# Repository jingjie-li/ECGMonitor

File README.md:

# Overview
This is a ECG/SPO2 Monitor Project. We mainly used TI's (Texas Instrument) [ADS1293](http://www.ti.com/product/ads1293)/[AFE4400](http://www.ti.com/product/AFE4400/description) analog front-end IC to acquire physiology data form human body, and used TI's [MSP430F149 MCU](http://www.ti.com/product/MSP430F149/description) to control these Chips, and send the data to our Android Smartphone App via TI's Bluetooth IC [CC2540](http://www.ti.com/product/CC2540/description). In our smartphone App, we can display ECG/PPG wavefore, compute & display SPO2,Heart Rate, and Heart Rate Variability(HRV), and control the hardware to running on different acquision mode (such as 3-Leads or 5-Leads mode).

To do so, we disigned and made a custome PCB using Autodesk EAGLE, did embedded system programing for MSP430 using IAR IDE, and some stuff about smartphone APP. We also had a 3D printed case for our circuit.

The major advantages of our system, is our outstanding power consumption performance. Our hardware only took about 300mW Power for Li-ion battery (about ~180mW for bluetooth). Also, our PCB is super portable, size less than 10-by-10cm.

We Shared the majority of our code and design files. Including MSP430 program, PCB layout, 3D printing models, and some APP code.

We do these stuff is for a [National BME(Biomedical Engineering) Competition for College Students](http://bmedesign.medmeeting.org/cn) in ShenZhen, China.

__On Aug 28, 2018: We just won the FIRST PRIZE in [National BME(Biomedical Engineering) Competition for College Students](http://bmedesign.medmeeting.org/cn) in ShenZhen, China. Which is the HIGHEST AWARD.__

__Fig 1 Our First Prize Trophy and Certification__

# Quick access of our sub-modules
+ [Main MCU Controling Code](https://github.com/celelion/ECGMonitor/blob/master/MSP430/AFE%26ADS_inter/main.c)
+ [PCB Layout](https://github.com/celelion/ECGMonitor/tree/master/PCB)
+ [APP](https://github.com/celelion/ECGMonitor/tree/master/APP_Design)
+ [3D Printed PCB Case](https://github.com/celelion/ECGMonitor/tree/master/Case)
+ [Processing Tools for Computer Debugging](https://github.com/celelion/ECGMonitor/tree/master/Analog_Front/EEGPPGdataRecTest)
+ [Arduino DUE based IC chip(ADS1293/AFE4400) SPI interface verification code](https://github.com/celelion/ECGMonitor/tree/master/Analog_Front/Arduino-TestFirmware)

# Features
## Characteristics and Technical Indexes
### ECG

+ Differential Input Voltage Range: -400 mV ~ +400 mV
+ Common-Mode Rejection Ratio(CMRR): >100 dB
+ Differential Input Resistance: 500 MΩ
+ Sampling Rate: 150 Hz

### Oximeter
+ Sampling Rate: 50 Hz

### Power Consumption
| Overall Power | Bluetooth | ADS-ECG Module | AFE-Oximeter Module | MSP430-MCU Module |
| ------ | ------ | ------ | ------ | ------ |
| 291.1103 mW | 177.7327 mW | 3.1984 mW | 93.0931 mW | 17.0861 mW |

# Development Team
+ Jingjie Li (jingjie.li.21@ucl.ac.uk) - Hardware, PCB Layout, Part of MSP430 Programming, Debugging tools using Processing IDE, 3D modeling for the case
+ Jinming Li (lijinmingli@foxmail.com) - MSP430 Programming, Testing
+ Haoyi Tao - Android APP Programming

We are all class of 2019 BME undergraduate student from Xi'an Jiaotong University

# Hardware (By Jingjie Li)

__Fig 2 The PCB layout of ECG/SPO2 Monitor Hardware__

We had a MainBoard, which contains mainly 5 modules, which is 
+ LDO Module for power supply; 
+ ADS Module for ECG; 
+ AFE Module for SPO2; 
+ MCU Module for controlling ;
+ Debugging module, for downloading program(BSL), Serial-USB conversion for a convenient debuging on PC using Processing IDE.

__Fig 3 Different parts and modules on our Main PCB__

## Power Tree

We used 4.8V Li-ion Battery or 5V USB to powering the whole system. 5V/4.8V is directly feed to USB chip CH340, and the Bluetooth Module. A TI LM1117 LDO chip proveide 3.3V power to ADS1293 ECG Module, and MSP430 MCU Module. 

__Fig 4 The Power Tree of our MainPCB__

Powering AFE4400 is a little bit more complicated, to give AFE4400 IC a much more stable voltage supply, we used a Ultra-Low-Noise, High-PSRR [TI TPS7A49](http://www.ti.com/product/TPS7A49/description) chip to provide 3V power for the AFE4400's digital supply (DIG SUP) pins. Then, we used a Low Noise 'Ceramic Stable' LDO [TI LP3878](http://www.ti.com/product/LP3878-ADJ/samplebuy) to provide 3.7v power for AFE4400 LED drive power supply pins (LED DRV). Using two chips, provided us a better isolation in AFE4400, which could minimize the voltage fluctuation interfere from ADS, MCU or AFE LED DRV parts.

## Connectors

For a common use, we choosed standard connectors and cables in our hardware design.

__Fig 5 Hardware Connectors__

For example, for ECG, we used Mindray Standard 6-Pins, 5-Leads ECG cables and connectors; For SPO2, we used the standrad DB9 SPO2 Probe connector. So, it will be easy for our users to find new replcement when old probe is damaged.

## Signal Flow in our PCB

__Fig 6 Signal Flow in our PCB__

In our hardware, we used MSP430 MCU to drive the SPI Bus (as a master device) to configrate ECG and SPO2 Chips (Write data on specific address), and read digital data form each chip.

The MSP430 MCU then compress, encode the sampled data to a long int, and send to the Bluetooth module (To smartphone APP) or a serial-USB debug module via UART.

MSP430 MCU also controled several indicator LED, which we could visulize the sampling rhythm (By flashing of the ADS/AFE LED). LEDs can also provided alarms such as ECG Lead off, SPO2 Cable off for us.

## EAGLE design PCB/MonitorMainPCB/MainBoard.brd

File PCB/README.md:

# ECGMonitor
Project

# PCB Stuff

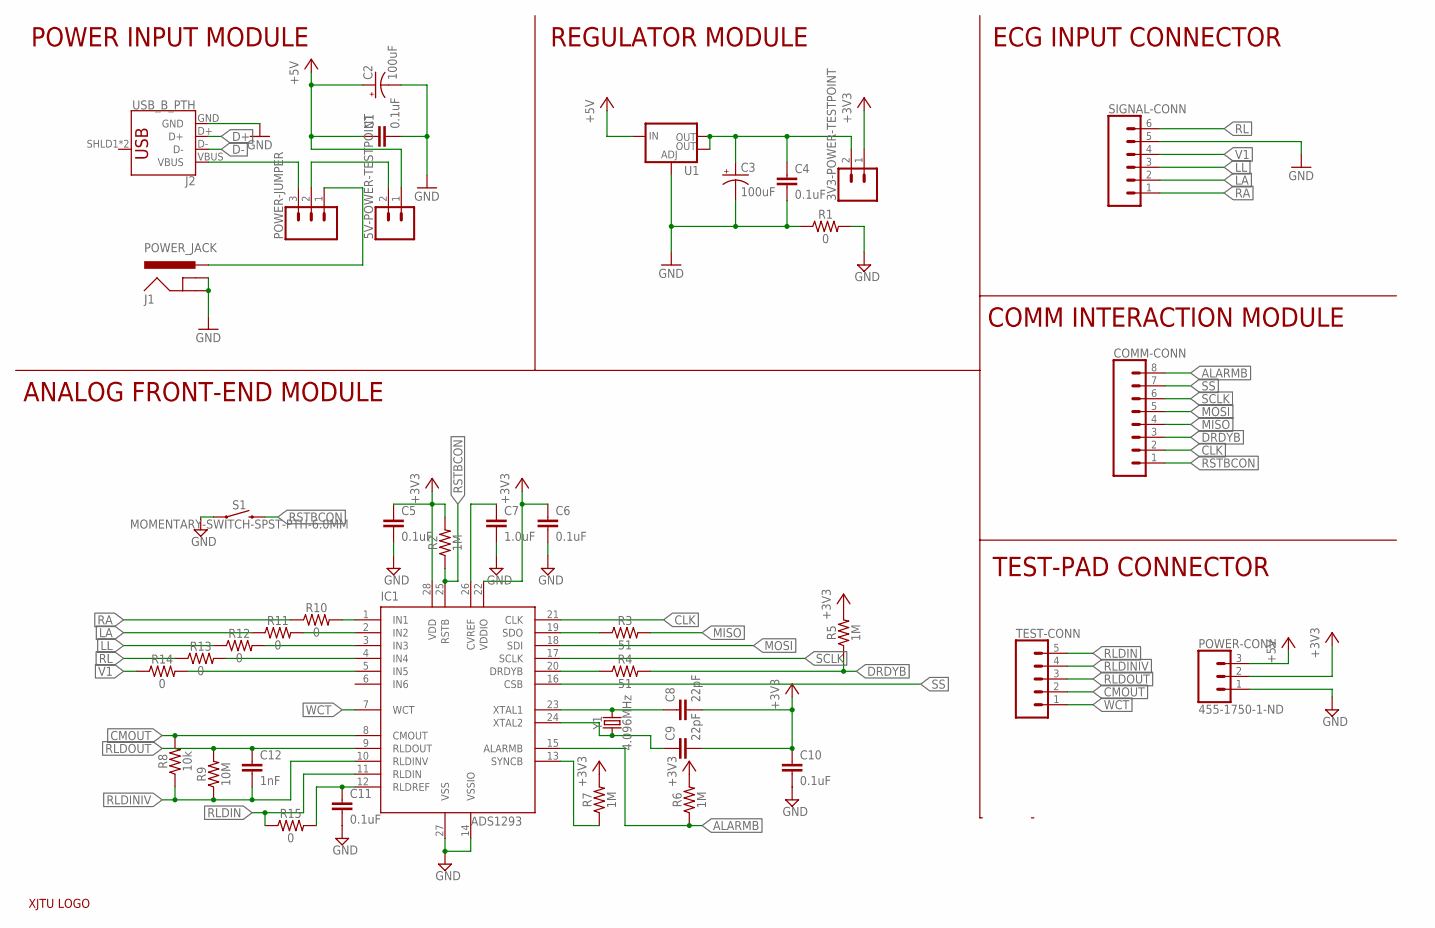
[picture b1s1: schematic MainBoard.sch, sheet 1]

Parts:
3V3-POWER-TESTPOINT, 5V-POWER-TESTPOINT: CONN_02; 1X02
C1, C4, C5, C6, C10, C11: 0.1uF; 0603
C2, C3: 100uF; CPOL-RADIAL-2.5MM-6.5MM
C7: 1.0uF; 0805
C8, C9: 22pF; 0603
C12: 1nF; 0603
COMM-CONN: CONN_08"; 1X08
IC1: ADS1293; QFN28-5X5
J1: POWER_JACK; POWER_JACK_PTH
J2: USB_B_PTH; USB-B-PTH
POWER-CONN: 455-1750-1-ND; 1X03
POWER-JUMPER: CONN_03; 1X03
R1, R10, R11, R12, R13, R14, R15: 0; 0603
R2, R5, R6, R7: 1M; 0603
R3, R4: 51; 0603
R8: 10k; 0603
R9: 10M; 0603
S1: MOMENTARY-SWITCH-SPST-PTH-6.0MM; TACTILE_SWITCH_PTH_6.0MM
SIGNAL-CONN: CONN_06POLAR; MOLEX-1X6
TEST-CONN: CONN_05; 1X05
U1: V_REG_LM1117SOT223; SOT223
U$6: XJTULOGO
Y1: 4.096MHz; HC49US

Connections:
+3V3: 3V3-POWER-TESTPOINT.1, C5.1, C6.1, C8.2, C9.2, C10.1, IC1.22 (VDDIO), IC1.28 (VDD), POWER-CONN.2, R2.2, R5.2, R6.2, R7.2; also elsewhere on the board
+5V: 5V-POWER-TESTPOINT.1, C1.1, C2.1 (+), POWER-CONN.3, U1.3 (IN); also elsewhere on the board
ALARMB: COMM-CONN.8, IC1.15 (ALARMB), R6.1; also elsewhere on the board
CLK: COMM-CONN.2, IC1.21 (CLK)
CMOUT: IC1.8 (CMOUT), R8.2, TEST-CONN.2
D+: J2.D+; also elsewhere on the board
D-: J2.D-; also elsewhere on the board
DRDYB: COMM-CONN.3, R4.2, R5.1; also elsewhere on the board
GND: C1.2, C2.2 (-), C3.2 (-), C4.2, C5.2, C6.2, C7.2, C10.2, C11.2, IC1.14 (VSSIO), IC1.27 (VSS), J1.GND, J1.GNDBREAK, J2.GND, POWER-CONN.1, R1.1, R1.2, S1.1, SIGNAL-CONN.5, U1.1 (ADJ); also elsewhere on the board
LA: R11.1, SIGNAL-CONN.2
LL: R12.1, SIGNAL-CONN.3
MISO: COMM-CONN.4, R3.2; also elsewhere on the board
MOSI: COMM-CONN.5, IC1.18 (SDI); also elsewhere on the board
unnamed: C7.1, IC1.26 (CVREF)
unnamed: J2.VBUS, POWER-JUMPER.3
unnamed: J1.PWR, POWER-JUMPER.1
unnamed: C8.1, IC1.23 (XTAL1), Y1.2
unnamed: C9.1, IC1.24 (XTAL2), Y1.1
unnamed: IC1.19 (SDO), R3.1
unnamed: IC1.20 (DRDYB), R4.1
unnamed: IC1.13 (SYNCB), R7.1
unnamed: C11.1, IC1.12 (RLDREF), R15.2
unnamed: IC1.1 (IN1), R10.2
unnamed: IC1.2 (IN2), R11.2
unnamed: IC1.3 (IN3), R12.2
unnamed: IC1.4 (IN4), R13.2
unnamed: IC1.5 (IN5), R14.2
unnamed: 5V-POWER-TESTPOINT.2, POWER-JUMPER.2
unnamed: 3V3-POWER-TESTPOINT.2, C3.1 (+), C4.1, U1.2 (OUT), U1.4 (OUT)
RA: R10.1, SIGNAL-CONN.1
RL: R13.1, SIGNAL-CONN.6
RLDIN: IC1.11 (RLDIN), R15.1, TEST-CONN.5
RLDINIV: C12.2, IC1.10 (RLDINV), R8.1, R9.1, TEST-CONN.4
RLDOUT: C12.1, IC1.9 (RLDOUT), R9.2, TEST-CONN.3
RSTBCON: COMM-CONN.1, IC1.25 (RSTB), R2.1, S1.3 (2)
SCLK: COMM-CONN.6, IC1.17 (SCLK); also elsewhere on the board
SS: COMM-CONN.7, IC1.16 (CSB); also elsewhere on the board
V1: R14.1, SIGNAL-CONN.4
WCT: IC1.7 (WCT), TEST-CONN.1

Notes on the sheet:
POWER INPUT MODULE
REGULATOR MODULE
ECG INPUT CONNECTOR
ANALOG FRONT-END MODULE
COMM INTERACTION MODULE
TEST-PAD CONNECTOR

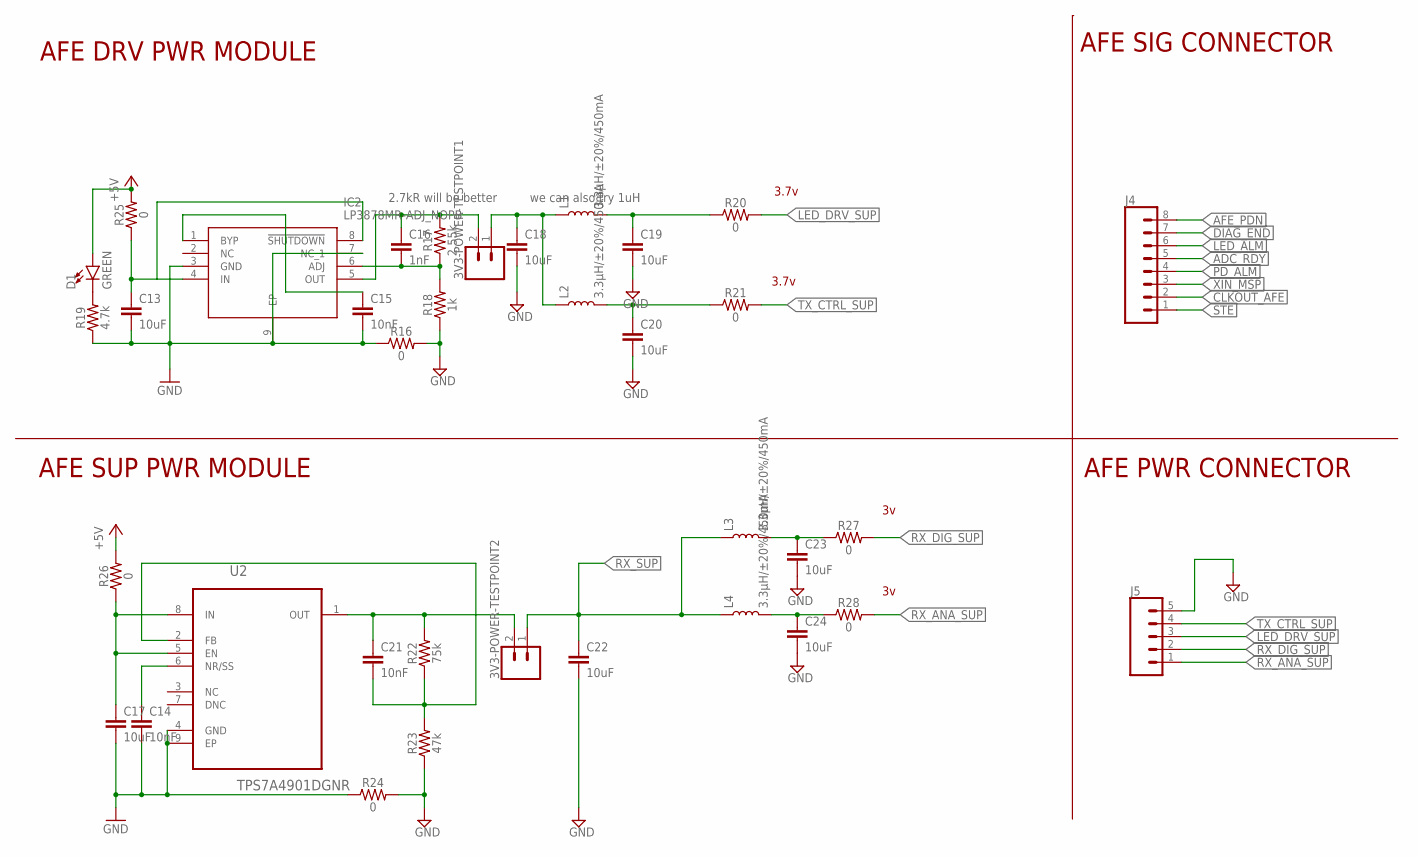
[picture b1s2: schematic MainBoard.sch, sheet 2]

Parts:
3V3-POWER-TESTPOINT1, 3V3-POWER-TESTPOINT2: CONN_02; 1X02
C13, C17, C18, C19, C20, C22, C23, C24: 10uF; 1206
C14, C15, C21: 10nF; 0603
C16: 1nF; 0603
D1: GREEN; LED-1206
IC2: LP3878MR-ADJ_NOPB; SOIC127P602X168-9N
J4: CONN_08"; 1X08
J5: CONN_05; 1X05
L1, L2, L3, L4: 3.3µH/±20%/450mA; 0805
R16, R20, R21, R24, R25, R26, R27, R28: 0; 0603
R17: 2.55k; 0603
R18: 1k; 0603
R19: 4.7k; 0603
R22: 75k; 0603
R23: 47k; 0603
U2: TPS7A4901DGNR; SOP65P490X110-9N

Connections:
+5V: D1.A, R25.2, R26.2; also elsewhere on the board
ADC_RDY: J4.5; also elsewhere on the board
AFE_PDN: J4.8; also elsewhere on the board
CLKOUT_AFE: J4.2; also elsewhere on the board
DIAG_END: J4.7; also elsewhere on the board
GND: C13.2, C14.2, C15.2, C17.2, C18.2, C19.2, C20.2, C22.2, C23.2, C24.2, IC2.3 (GND), IC2.7 (NC_1), IC2.9 (EP), J5.5, R16.1, R16.2, R18.1, R19.1, R23.1, R24.1, R24.2, U2.4 (GND), U2.9 (EP); also elsewhere on the board
LED_ALM: J4.6; also elsewhere on the board
LED_DRV_SUP: J5.3, R20.2; also elsewhere on the board
unnamed: D1.C, R19.2
unnamed: 3V3-POWER-TESTPOINT1.1, C18.1, L1.1, L2.1
unnamed: C16.2, IC2.6 (ADJ), R17.1, R18.2
unnamed: C15.1, IC2.1 (BYP)
unnamed: 3V3-POWER-TESTPOINT1.2, C16.1, IC2.5 (OUT), R17.2
unnamed: C14.1, U2.6 (NR/SS)
unnamed: C19.1, L1.2, R20.1
unnamed: C20.1, L2.2, R21.1
unnamed: C17.1, R26.1, U2.5 (EN), U2.8 (IN)
unnamed: 3V3-POWER-TESTPOINT2.2, C21.1, R22.2, U2.1 (OUT)
unnamed: C21.2, R22.1, R23.2, U2.2 (FB)
unnamed: C23.1, L3.2, R27.1
unnamed: C13.1, IC2.4 (IN), IC2.8 (!SHUTDOWN), R25.1
unnamed: C24.1, L4.2, R28.1
PD_ALM: J4.4; also elsewhere on the board
RX_ANA_SUP: J5.1, R28.2; also elsewhere on the board
RX_DIG_SUP: J5.2, R27.2; also elsewhere on the board
RX_SUP: 3V3-POWER-TESTPOINT2.1, C22.1, L3.1, L4.1
STE: J4.1; also elsewhere on the board
TX_CTRL_SUP: J5.4, R21.2; also elsewhere on the board
XIN_MSP: J4.3; also elsewhere on the board

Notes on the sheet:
2.7kR will be better
we can also try 1uH
AFE SUP PWR MODULE
AFE DRV PWR MODULE
AFE SIG CONNECTOR
AFE PWR CONNECTOR
3.7v

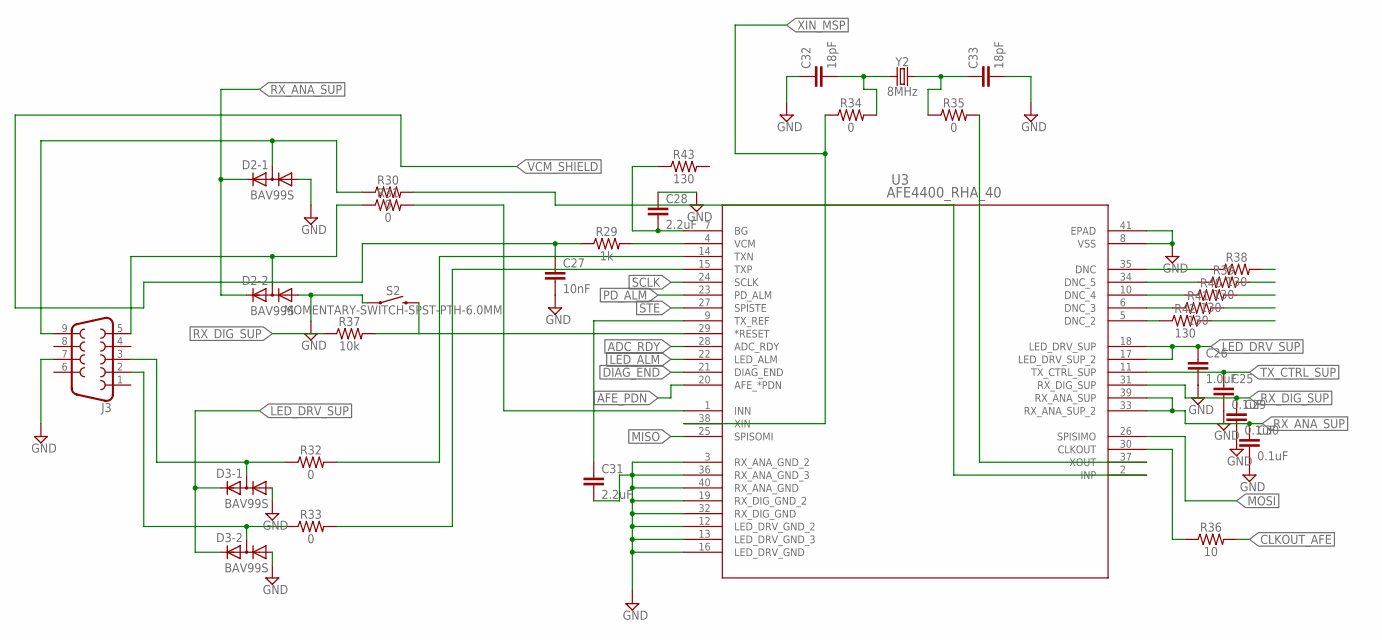
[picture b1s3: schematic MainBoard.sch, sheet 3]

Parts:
C25, C29, C30: 0.1uF; 0603
C26: 1.0uF; 0805
C27: 10nF; 0603
C28, C31: 2.2uF; 0805
C32, C33: 18pF; 0603
D2, D3: BAV99S; SOT363
J3: DB9FEMALE; DB9
R29: 1k; 0603
R30, R31, R32, R33, R34, R35: 0; 0603
R36: 10; 0603
R37: 10k; 0603
R38, R39, R40, R41, R42, R43: 130; 0603
S2: MOMENTARY-SWITCH-SPST-PTH-6.0MM; TACTILE_SWITCH_PTH_6.0MM
U3: AFE4400_RHA_40; RHA40_4P15X4P15
Y2: 8MHz; CRYSTAL-SMD-5X3.2-4PAD

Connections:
ADC_RDY: U3.28 (ADC_RDY); also elsewhere on the board
AFE_PDN: U3.20 (AFE_*PDN); also elsewhere on the board
CLKOUT_AFE: R36.2; also elsewhere on the board
DIAG_END: U3.21 (DIAG_END); also elsewhere on the board
GND: C25.2, C26.2, C27.2, C28.1, C29.2, C30.2, C31.2, C32.1, C33.2, D2.1 (A1), D2.4 (A1), D3.1 (A1), D3.4 (A1), J3.7, S2.1, U3.3 (RX_ANA_GND_2), U3.8 (VSS), U3.12 (LED_DRV_GND_2), U3.13 (LED_DRV_GND_3), U3.16 (LED_DRV_GND), U3.19 (RX_DIG_GND_2), U3.32 (RX_DIG_GND), U3.36 (RX_ANA_GND_3), U3.40 (RX_ANA_GND), U3.41 (EPAD); also elsewhere on the board
LED_ALM: U3.22 (LED_ALM); also elsewhere on the board
LED_DRV_SUP: C26.1, D3.2 (K2), D3.5 (K2), U3.17 (LED_DRV_SUP_2), U3.18 (LED_DRV_SUP); also elsewhere on the board
MISO: U3.25 (SPISOMI); also elsewhere on the board
MOSI: U3.26 (SPISIMO); also elsewhere on the board
unnamed: C28.2, R43.1, U3.7 (BG)
unnamed: C31.1, U3.9 (TX_REF)
unnamed: R32.2, U3.14 (TXN)
unnamed: R29.2, U3.4 (VCM)
unnamed: R31.2, U3.1 (INN)
unnamed: R30.2, U3.2 (INP)
unnamed: D2.3 (K1A2), J3.5, R31.1
unnamed: D2.6 (K1A2), J3.9, R30.1
unnamed: R33.2, U3.15 (TXP)
unnamed: D3.6 (K1A2), J3.3, R32.1
unnamed: D3.3 (K1A2), J3.2, R33.1
unnamed: C32.2, R34.2, Y2.1
unnamed: C33.1, R35.1, Y2.3 (2)
unnamed: R36.1, U3.30 (CLKOUT)
unnamed: R37.2, S2.3 (2), U3.29 (*RESET)
unnamed: R35.2, U3.37 (XOUT)
unnamed: R38.1, U3.35 (DNC)
unnamed: R42.1, U3.5 (DNC_2)
unnamed: R41.1, U3.6 (DNC_3)
unnamed: R40.1, U3.10 (DNC_4)
unnamed: R39.1, U3.34 (DNC_5)
PD_ALM: U3.23 (PD_ALM); also elsewhere on the board
RX_ANA_SUP: C30.1, D2.2 (K2), D2.5 (K2), U3.33 (RX_ANA_SUP_2), U3.39 (RX_ANA_SUP); also elsewhere on the board
RX_DIG_SUP: C29.1, R37.1, U3.31 (RX_DIG_SUP); also elsewhere on the board
SCLK: U3.24 (SCLK); also elsewhere on the board
STE: U3.27 (SPISTE); also elsewhere on the board
TX_CTRL_SUP: C25.1, U3.11 (TX_CTRL_SUP); also elsewhere on the board
VCM_SHIELD: C27.1, R29.1
XIN_MSP: R34.1, U3.38 (XIN); also elsewhere on the board

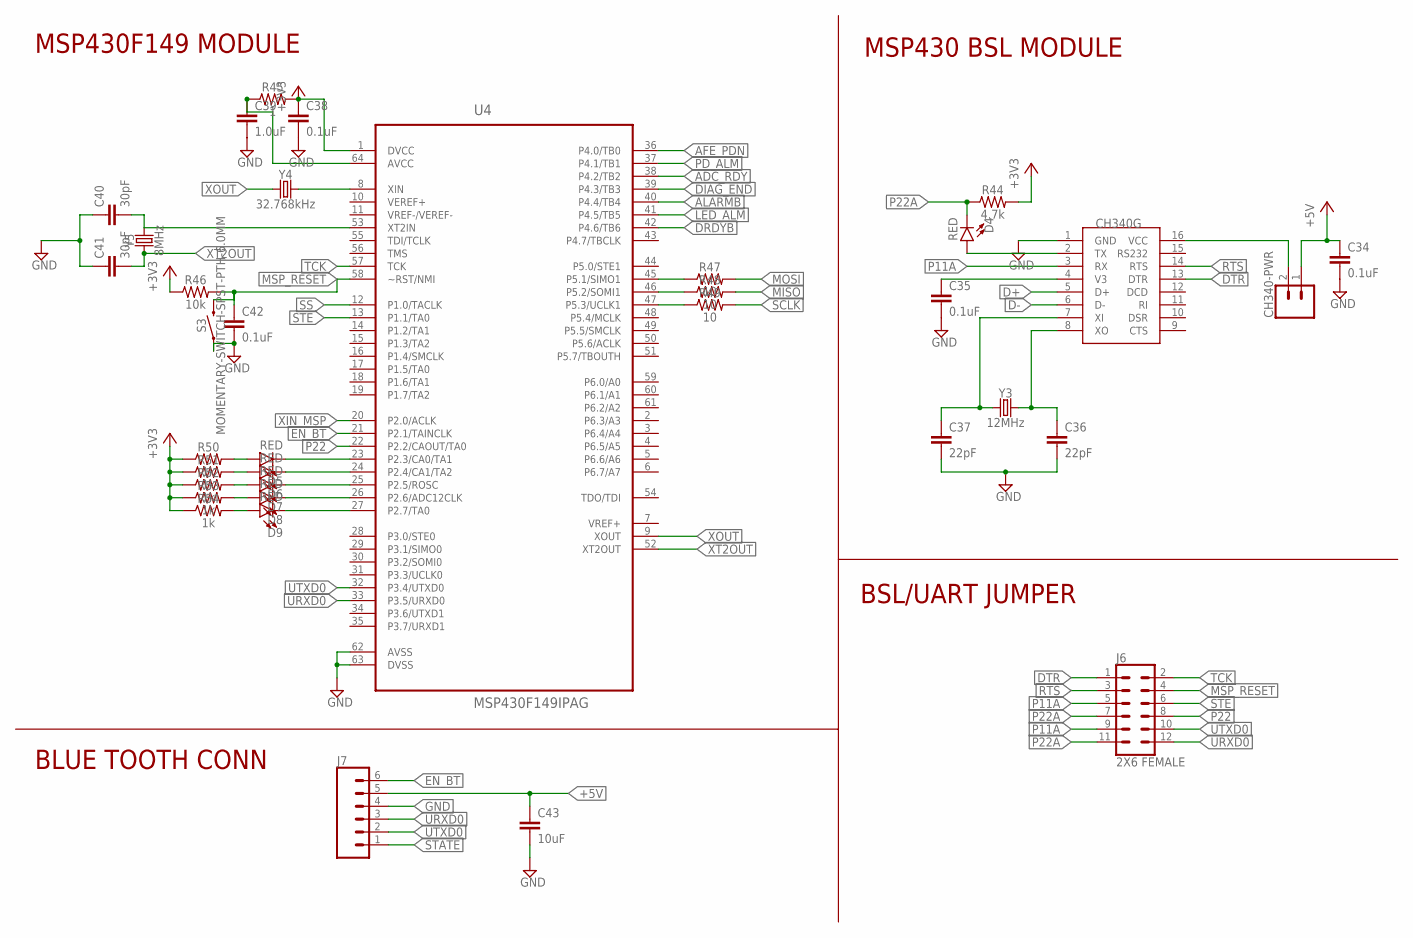
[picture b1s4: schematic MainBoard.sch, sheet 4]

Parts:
C34, C35, C38, C42: 0.1uF; 0603
C36, C37: 22pF; 0603
C39: 1.0uF; 0603
C40, C41: 30pF; 0603
C43: 10uF; 1206
CH340-PWR: CONN_02; 1X02
D4, D5, D6, D7, D8, D9: RED; LED-0603
J6: 2X6 FEMALE; 2X6
J7: CONN_06SILK_FEMALE_PTH; 1X06
R44: 4.7k; 0603
R45: 1; 0603
R46: 10k; 0603
R47, R48, R49: 10; 0603
R50, R51, R52, R53, R54: 1k; 0603
S3: MOMENTARY-SWITCH-SPST-PTH-6.0MM; TACTILE_SWITCH_PTH_6.0MM
U4: MSP430F149IPAG; QFP50P1200X1200X120-64N
U$5: CH340G; SOIC16
Y3: 12MHz; CRYSTAL-SMD-5X3.2-4PAD
Y4: 32.768kHz; CRYSTAL-SMD-3.2X1.5MM
Y5: 8MHz; CRYSTAL-SMD-5X3.2-4PAD

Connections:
+3V3: C38.1, R44.2, R45.2, R46.1, R50.1, R51.1, R52.1, R53.1, R54.1, U4.1 (DVCC); also elsewhere on the board
+5V: C34.1, C43.1, CH340-PWR.1, J7.5; also elsewhere on the board
ADC_RDY: U4.38 (P4.2/TB2); also elsewhere on the board
AFE_PDN: U4.36 (P4.0/TB0); also elsewhere on the board
ALARMB: U4.40 (P4.4/TB4); also elsewhere on the board
D+: U$5.5 (D+); also elsewhere on the board
D-: U$5.6 (D-); also elsewhere on the board
DIAG_END: U4.39 (P4.3/TB3); also elsewhere on the board
DRDYB: U4.42 (P4.6/TB6); also elsewhere on the board
DTR: J6.1, U$5.13 (DTR)
EN_BT: J7.6, U4.21 (P2.1/TAINCLK)
GND: C34.2, C35.2, C36.2, C37.2, C38.2, C39.2, C40.1, C41.1, C42.2, C43.2, J7.4, S3.1, U4.62 (AVSS), U4.63 (DVSS), U$5.1 (GND); also elsewhere on the board
LED_ALM: U4.41 (P4.5/TB5); also elsewhere on the board
MISO: R48.2; also elsewhere on the board
MOSI: R47.2; also elsewhere on the board
MSP_RESET: C42.1, J6.4, R46.2, S3.3 (2), U4.58 (~RST/NMI)
unnamed: C39.1, R45.1, U4.64 (AVCC)
unnamed: R47.1, U4.45 (P5.1/SIMO1)
unnamed: C35.1, U$5.4 (V3)
unnamed: D4.A, U$5.2 (TX)
unnamed: U4.8 (XIN), Y4.P$2 (2)
unnamed: C40.2, U4.53 (XT2IN), Y5.3 (2)
unnamed: R48.1, U4.46 (P5.2/SOMI1)
unnamed: R49.1, U4.47 (P5.3/UCLK1)
unnamed: D5.C, U4.23 (P2.3/CA0/TA1)
unnamed: D6.C, U4.24 (P2.4/CA1/TA2)
unnamed: D7.C, U4.25 (P2.5/ROSC)
unnamed: D8.C, U4.26 (P2.6/ADC12CLK)
unnamed: D9.C, U4.27 (P2.7/TA0)
unnamed: D5.A, R50.2
unnamed: D6.A, R51.2
unnamed: D7.A, R52.2
unnamed: D8.A, R53.2
unnamed: D9.A, R54.2
unnamed: CH340-PWR.2, U$5.16 (VCC)
P11A: J6.5, J6.9, U$5.3 (RX)
P22: J6.8, U4.22 (P2.2/CAOUT/TA0)
P22A: D4.C, J6.7, J6.11, R44.1
PD_ALM: U4.37 (P4.1/TB1); also elsewhere on the board
RTS: J6.3, U$5.14 (RTS)
SCLK: R49.2; also elsewhere on the board
SS: U4.12 (P1.0/TACLK); also elsewhere on the board
STATE: J7.1
STE: J6.6, U4.13 (P1.1/TA0); also elsewhere on the board
TCK: J6.2, U4.57 (TCK)
URXD0: J6.12, J7.3, U4.33 (P3.5/URXD0)
UTXD0: J6.10, J7.2, U4.32 (P3.4/UTXD0)
XI: C37.1, U$5.7 (XI), Y3.1
XIN_MSP: U4.20 (P2.0/ACLK); also elsewhere on the board
XO: C36.1, U$5.8 (XO), Y3.3 (2)
XOUT: U4.9 (XOUT), Y4.P$1 (1)
XT2OUT: C41.2, U4.52 (XT2OUT), Y5.1

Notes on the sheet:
MSP430F149 MODULE
MSP430 BSL MODULE
BSL/UART JUMPER
BLUE TOOTH CONN

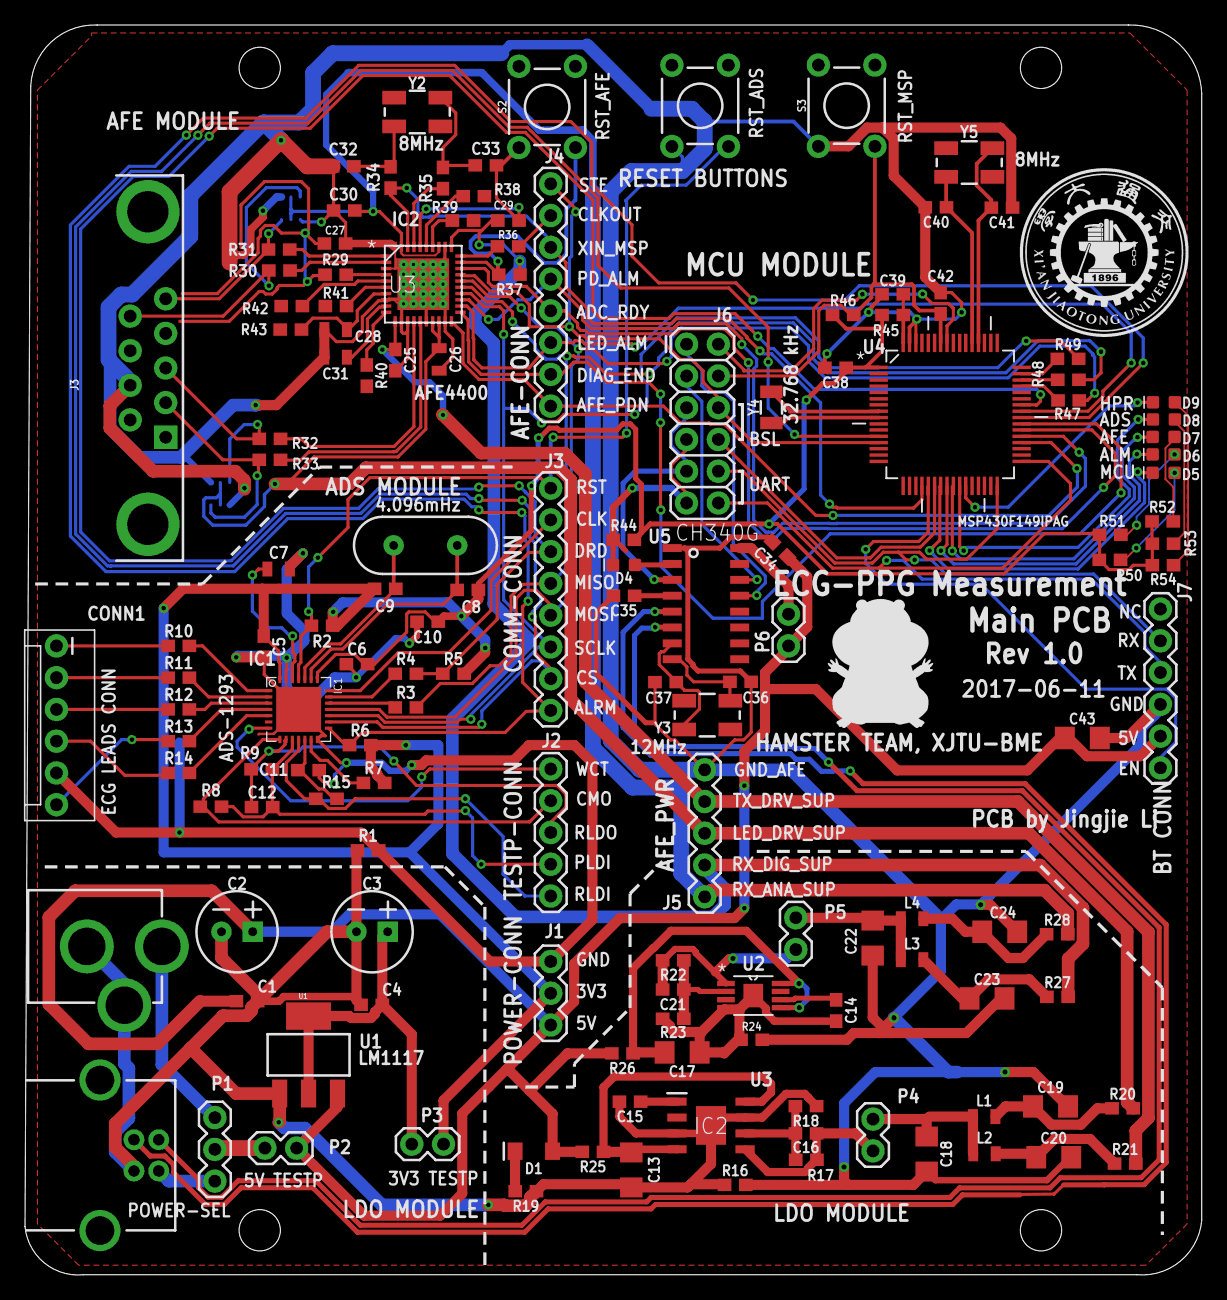
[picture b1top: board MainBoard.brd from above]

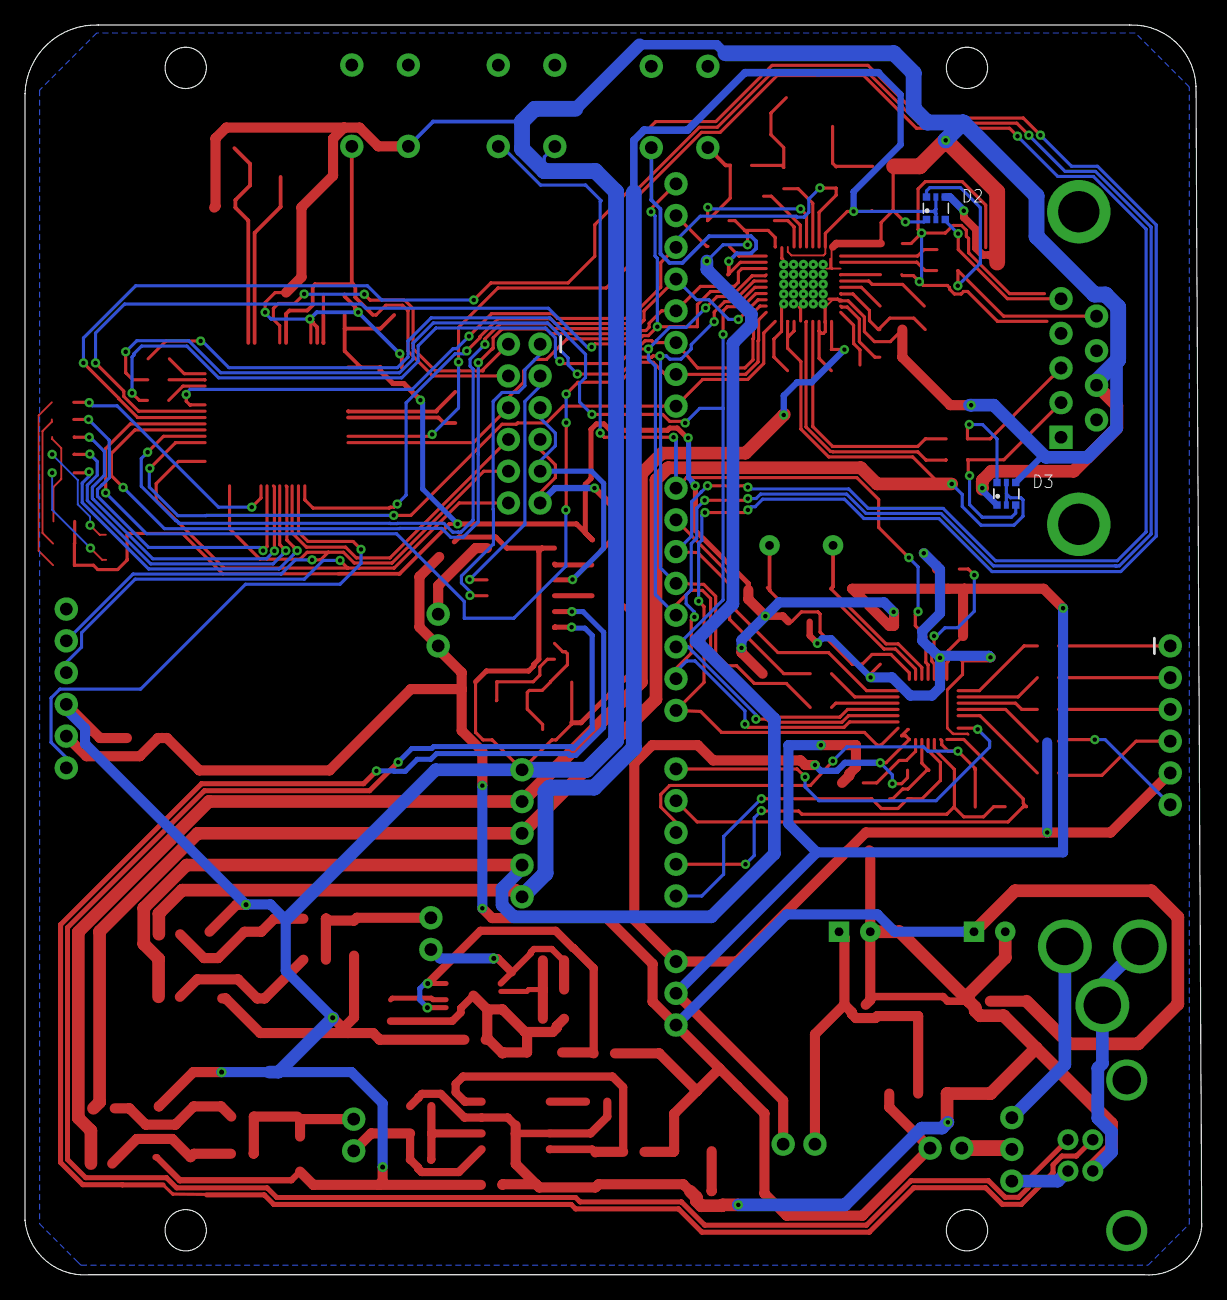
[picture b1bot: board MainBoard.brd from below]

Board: 2 copper layers, 94.1 x 100.0 mm, 148 parts (2 on the bottom side), 121 nets.

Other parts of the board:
U$1, U$2, U$3, U$4: STAND-OFF
U$7: HAMSTERLOGO

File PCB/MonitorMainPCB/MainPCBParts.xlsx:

心电-血氧监测系统元件列表
元件 | 位号 | 每片数量
贴片电容 0.1uF-0603 | C1,C4,C5,C6,C10,C11,C25,C29,C30,C34,C35,C38,C42 | 13
直插电容100uF | C2,C3 | 2
贴片电容1.0uF-0603 | C7,C26,C39 | 3
贴片电容22pF-0603 | C8,C9,C36,C37 | 4
贴片电容1nF-0603 | C12,C16 | 2
贴片电容10uF-1206 | C13,C17,C18,C19,C20,C22,C23,C24,C43 | 9
贴片电容10nF-0603 | C14,C15,C21,C27 | 4
贴片电容2.2uF-0603 | C28,C31 | 2
贴片电容-18pF-0603 | C32,C33 | 2
贴片电容-30pF-0603 | C40,C41 | 2
贴片LED-绿色-1206 | D1 | 1
贴片LED-红色-0603 | D5,D6,D7,D8,D9 | 6
贴片开关二极管-BAV99S-SOT363 | D2,D3 | 2
贴片电感 3.3uH/450mA-0805 | L1,L2,L3,L4 | 4
贴片电感 1uH/450mA-0805 | 无 | 4
贴片电阻0R-0603 | R1,R3,R10,R11,R12,R13,R14,R15,R16,R20,R21,R24,R25,R26,R27,R28,R30,R31,R32,R33,R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 | 21
贴片电阻1M欧-0603 | R2,R5,R6,R7 | 4
贴片电阻51欧-0603 | R4 | 2
贴片电阻10k欧-0603 | R8,R37,R46 | 3
贴片电阻10M欧-0603 | R9 | 1
贴片电阻2.55k欧-0603 | R17 | 1
贴片电阻1k欧-0603 | R18,R29,R50,R51,R52,R53,R54 | 7
贴片电阻4.7k欧-0603 | R19,R44 | 2
贴片电阻75k欧-0603 | R22 | 1
贴片电阻47k欧-0603 | R23 | 1
贴片电阻10欧-0603 | R36,R47,R48,R49 | 4
贴片电阻130欧-0603 | R38,R39,R40,R41,R42,R43 | 6
贴片电阻1欧-0603 | R45 | 1
直插晶震4.096MHz-HC49S封装 | Y1 | 1
贴片晶震8MHz-5X3.2-4脚 | Y2,Y5 | 2
贴片晶震12MHz-5X3.2-4脚 | Y3 | 1
贴片晶震32.768kHz-3.2X1.5MM | Y4 | 1
芯片MSP430F149IPAG，QFP50P1200X1200X120-64N封装 | U4 | 1
芯片AFE4400_RHA_40，RHA40_4P15X4P15封装 | IC2 | 1
芯片CH340G，SOIC16封装 | U5 | 1
芯片TPS7A4901DGNR，SOP65P490X110-9N封装 | U2 | 1
芯片LP3878MR-ADJ_NOPB，SOIC127P602X168-9N封装 | U3 | 1
芯片ADS1293，QFN28-5X5封装 | IC1 | 1
稳压芯片LM1117 3.3v，SOT223封装 | U1 | 1
DC电源插座5.5-2.1mm 直插 | J1 | 1
USB-B型 母座，直插 | J2 | 1
DB9母座，直插 | J3 | 1
2.54mm单排直插排针 | J4,J5 | 0
2.54mm双排排针 | J6 | 5
2.54mm长针单排母座 | J7 | 1
直插按键5mm*5mm*6 | S1,S2,S3 | 3

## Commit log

2018-04-26 Add sub-project folders and set-up readme
2018-04-26 add ADS1298 Manual PDF
2018-04-26 add MSP430 link stuff
2018-04-26 correction
2018-04-26 add overall guide pdf
2018-05-09 start-up of the pcb projects
2018-05-09 Add TI ADS1293 stuff
2018-05-09 add afe4400 stuff
2018-05-09 edit pdf links
2018-05-14 changed assignment
    by jinming
2018-05-14 pcb stuff
2018-05-14 blueteeth&msp430
2018-05-14 msp430_datasheet&codes
2018-05-14 MSP430_IAR
2018-05-14 add BOM
2018-05-17 some AFE PCB Stuff
2018-05-17 Init Account Book
2018-05-17 edit markdown table
2018-05-19 blue&uart
2018-05-19 fapiao
2018-05-20 ECGMonitor app version 1.0
2018-05-23 delete
    nothing
2018-05-24 ADS&AFE
2018-05-24 Add Arduino ADS1293 test code
2018-05-27 afe4400 pcb stuff
2018-05-27 almost complete AFE PCB
2018-05-28 add matlab data for dealing with egg signal
2018-05-29 Finishing ADS&AFE joint test pcb
    exporting gerber
2018-05-29 Add PCB money
2018-05-30 doing main PCB stuff
2018-05-30 ads_reg
2018-05-31 finishing Main PCB
2018-05-31 main PCB finished
2018-06-01 finished main PCB
2018-06-05 update some kind of mianPCB
2018-06-05 MONEY
2018-06-05 Revert "Merge branch 'master' of https://github.com/celelion/ECGMonitor"
    This reverts commit f7783cc06e649bc8b4ab999284b80d95ebf74241, reversing
    changes made to 6526a36a7f04e243d33003dbca553b52cb26d685.
2018-06-06 ADS1293 SPI FINISHING CODE
2018-06-06 clearing
2018-06-06 moving folder
2018-06-10 AFE Test Arduino code
2018-06-11 Fianl Complete of MainPCB
2018-06-11 cleaning main PCB stuff
2018-06-12 START WORKING ON AFE4400 MSP CODE
2018-06-14 update AFE code
2018-06-15 afe4400
2018-06-15 update code
    update code as you wish
2018-06-20 Revert "Merge branch 'master' of https://github.com/celelion/ECGMonitor"
    This reverts commit 03ee45a00087e1037af98fd14dcddaf7bce1beab, reversing
    changes made to 92617abf44b60358c4d8b3ab7076f1124fd72dac.
2018-06-20 Revert "Merge branch 'master' of https://github.com/celelion/ECGMonitor"
    This reverts commit c44e58daf1784b5ce08a81c80536002421c09fa8, reversing
    changes made to d45c217e6ac5a4944619fff0b1c0d4002a2e113a.
2018-06-20 update PCB stuff
2018-06-21 AFE&ADS
2018-06-22 SBzhou
2018-06-23 Fix STE pins out & Add state indicator LED
2018-06-23 Some Personal Notes
2018-06-23 Add processing GUI code
2018-06-23 update ADS code
2018-06-24 Add EEGPPG Joint test code
2018-06-24 jinmingdev init
2018-06-25 edit BOM
    R3->0R
    10uf capacitors->1206 package
2018-06-25 add auto baseline-correction code
2018-06-25 solved int problem
2018-06-25 inter
2018-06-25 using thread to compute data & do paint stuff
2018-06-25 edit Timer CCR1 params
2018-06-26 ADSINTER
2018-06-26 fixed multi-trigger problem
2018-06-26 AFEINTER
2018-06-27 150Hz is okay now
2018-06-30 pcb pdf
2018-07-31 biaozhu
2018-07-31 sampling rate
2018-07-31 xueyang
2018-08-02 restart
2018-08-07 use_inter1
2018-08-08 delete
2018-08-09 cleaning
2018-08-09 add gitignore file
2018-08-09 add ignore
2018-08-09 ignore more files
2018-08-09 stuff
2018-08-09 update gitignore
2018-08-09 test gitignore
2018-08-09 add serial code recieving function while running
2018-08-09 add reset exit flag to zero
2018-08-09 Move char read out of the main loop
2018-08-09 feng
2018-08-10 change1
2018-08-10 Revert "change1"
    This reverts commit e374bdcf2a19593038c1f26108a3193d100030f4.
2018-08-10 Revert "Revert "change1""
    This reverts commit b5471e9ee17f9e02246be68ecf8bf1a2891a3d38.
2018-08-10 delete_annotation
2018-08-10 set3set5
2018-08-10 set3pdf
2018-08-11 put UART write Long in a function
2018-08-11 add lead selection functions
2018-08-11 add leadoff functions in M&P Mode
2018-08-11 update processing code
2018-08-11 remove mouse logo
2018-08-17 add new version app
2018-08-18 fix some bugs
2018-08-19 done functional switching functions
2018-08-19 FIX BUG
2018-08-19 FIXED A BUG
2018-08-19 close ADS & AFE in Test Mode
2018-08-19 cleaning PCB stuff
2018-08-19 Add PowerTree Parts in readme
2018-08-19 add connectors section and signal flow sections
2018-08-20 Add a 3d print case for our main PCB
2018-08-20 3CHANNEL&SPO2
2018-08-20 add computer debug flag
2018-08-20 修复AFE\ADS only 模式下波形显示问题
2018-08-20 stop sending in test mode
2018-08-21 Power Consumption Ana Data
2018-08-24 ECG Leadoff not sending
2018-08-24 Shutdown Leadoff detection in AFEonly Mode
2018-08-24 add links for ADS/AFE/MSP
2018-08-26 case pic
2018-08-28 update award info
2018-09-07 account of lijinming
2018-09-07 account 2
2018-09-16 comments
2018-09-26 remove unrelated fee
2018-09-29 change comments
2018-10-03 add First Prize Trophy and Certification pics

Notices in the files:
parts and their libraries:
SparkFun-Capacitors: Licensing: Creative Commons ShareAlike 4.0 International - https://creativecommons.org/licenses/by-sa/4.0
